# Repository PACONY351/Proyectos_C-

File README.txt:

Este repositorio tiene como fin almacenar de forma estructurada los proyectos
elaborados dentro del mismo, los cuales van desde lo fundamental a lo especial

				Gracias y suerte!!

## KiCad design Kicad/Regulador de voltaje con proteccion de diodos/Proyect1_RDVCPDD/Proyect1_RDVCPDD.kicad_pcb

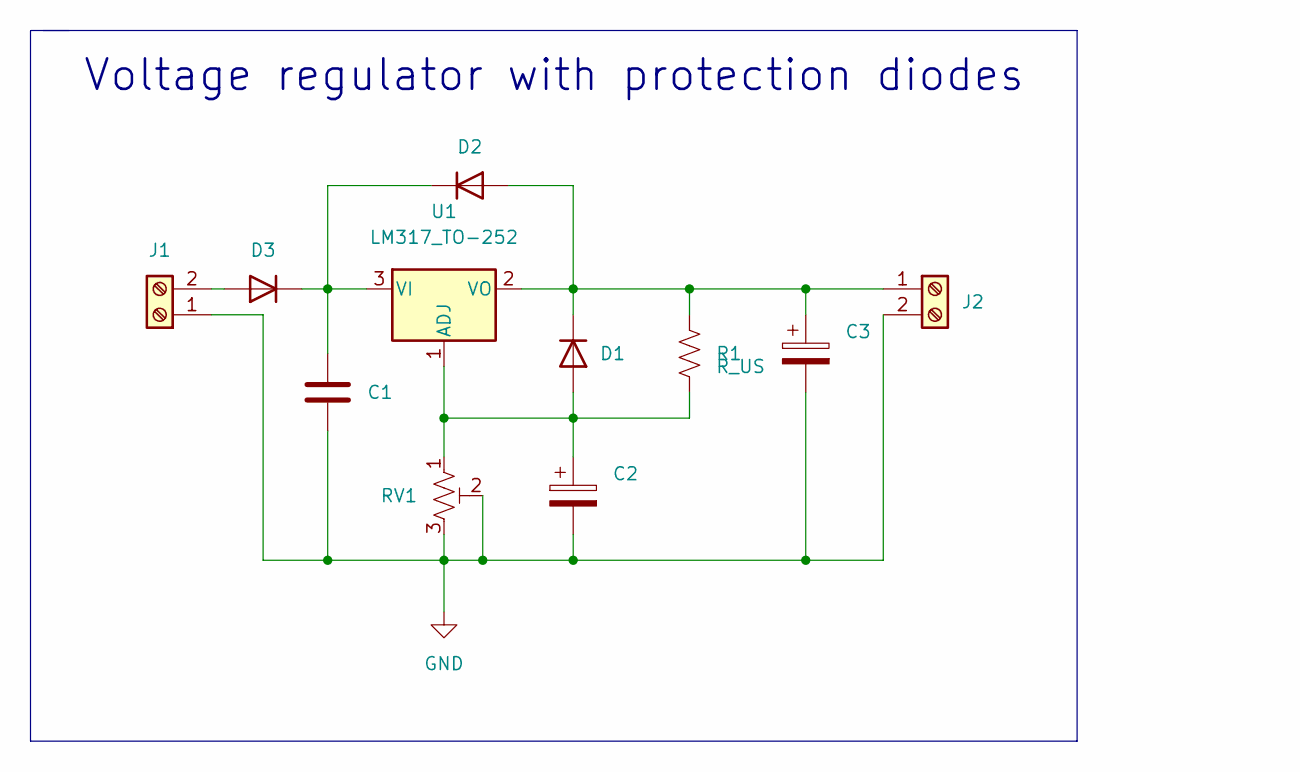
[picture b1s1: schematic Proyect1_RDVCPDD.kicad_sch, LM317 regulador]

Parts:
C1: C; C_0603_1608Metric
C2, C3: C_Polarized; CP_Elec_6.3x5.8
D1, D2, D3: DIODE; D_SMA
J1, J2: Screw_Terminal_01x02; TerminalBlock_Phoenix_MKDS-1,5-2-5.08_1x02_P5.08mm_Horizont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
R1: R_US; R_1206_3216Metric
RV1: R_Potentiometer_Trim_US; Potentiometer_Bourns_3296W_Vertical
U1: LM317_TO-252; TO-252-2

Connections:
GND: C1.2, C2.2, C3.2, J1.1, J2.2, RV1.2, RV1.3
unnamed: C1.1, D2.2 (K), D3.2 (K), U1.3 (VI)
unnamed: C2.1, D1.1 (A), R1.2, RV1.1, U1.1 (ADJ)
unnamed: C3.1, D1.2 (K), D2.1 (A), J2.1, R1.1, U1.2 (VO)
unnamed: D3.1 (A), J1.2

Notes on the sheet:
Voltage regulator with protection diodes

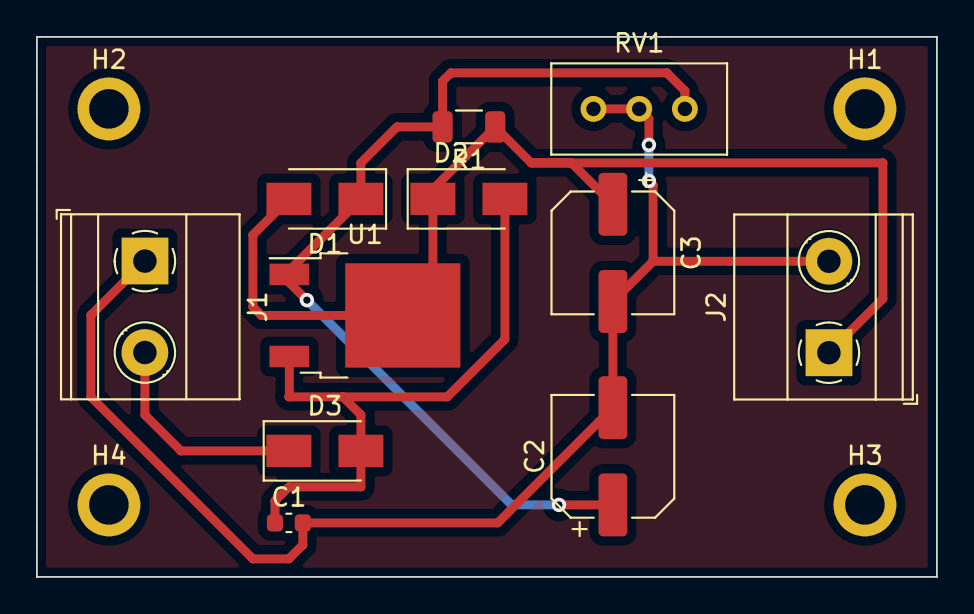
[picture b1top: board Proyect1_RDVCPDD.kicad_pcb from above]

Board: 2 copper layers, 50.0 x 30.0 mm, 15 parts (0 on the bottom side), 5 nets.

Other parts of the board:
H1, H2, H3, H4: MountingHole_2.2mm_M2_ISO7380_Pad

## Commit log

2025-02-20 frist commit
2025-02-20 [ADD] Hola.html
2025-02-20 [UPDATE] Hola.html
2025-02-21 [TEST]
2025-02-21 [UPDATE] HolaMundo.cpp
2025-02-22 [ADD] Ej1
2025-02-22 [UPDATE] Ej1.cpp
2025-02-22 [ADD] Pr2 Ej1.cpp
2025-02-22 [UPDATE] Pr3 Ej1
2025-02-24 [ADD] Pr5 Ej1
2025-02-24 [ADD] Pr7 Ej1
2025-02-25 [ADD] Pr8 Ej1
2025-03-02 [ADD] Calculadora
2025-03-03 [UPDATE] Pr8
2025-03-03 [ADD] Pr9 Ej1
2025-03-03 [UPDATE] Pr9
2025-03-03 [ADD] Pr10
2025-03-03 [ADD] Pr11
2025-03-10 [ADD] Punteros/Pr1/Ej1.cpp
2025-03-10 [UPDATE] Punteros/Pr1/Ej1
2025-03-11 [UPDATE] Punteros/Pr1/Ej1.cpp
2025-03-13 [ADD] Pilas/Intro/intro.cpp
2025-03-13 [UPDATE] Pilas/Intro/intro.cpp
2025-03-13 [UPDATE] Punteros/Intro/intro.cpp
2025-03-13 [ADD] Colas/Intro/intro.cpp and [UPDATE] Pilas/Intro/intro.cpp
2025-03-13 [UPDATE] Colas/Intro/intro.cpp
2025-03-13 [UPDATE] Colas/Intro/intro.cpp and [ADD] Colas/Pr1/Ej1.cpp
2025-03-13 [UPDATE] Colas/Pr1/Ej1.cpp
2025-03-14 [ADD] POO/Pr1,Pr2,Pr3
2025-03-20 [ADD] Solo_C/Pr1/Ej1.c Ej1 main
2025-03-24 [ADD] STM32Cube/Introducción/Introduccion*
2025-03-24 [UPDATE] Introduccion*
2025-03-24 [ADD] PunterosEnPIC/main.c
2025-04-03 [ADD] Kicad *
2025-04-03 [UPDATE] Kicad *
2025-04-05 [UPDATE] Kicad/Pr1 *
2025-04-19 [ADD] Arduino*
2025-04-19 [ADD] Pr2_Control_Led_Wifi *
2025-04-20 [ADD] Arduno/Pr4 *
2025-04-20 [ADD] Arduino/Pr4 Control_datos_por_Wifi *
2025-04-21 [ADD] Arduino/Pr5_Contro_Led_Servo *
2025-05-12 [ADD] Fundamentos_Basicos_C#*
